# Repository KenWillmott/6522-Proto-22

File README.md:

# 6522-Proto-22
6522 VIA and prototyping board for M8 bus

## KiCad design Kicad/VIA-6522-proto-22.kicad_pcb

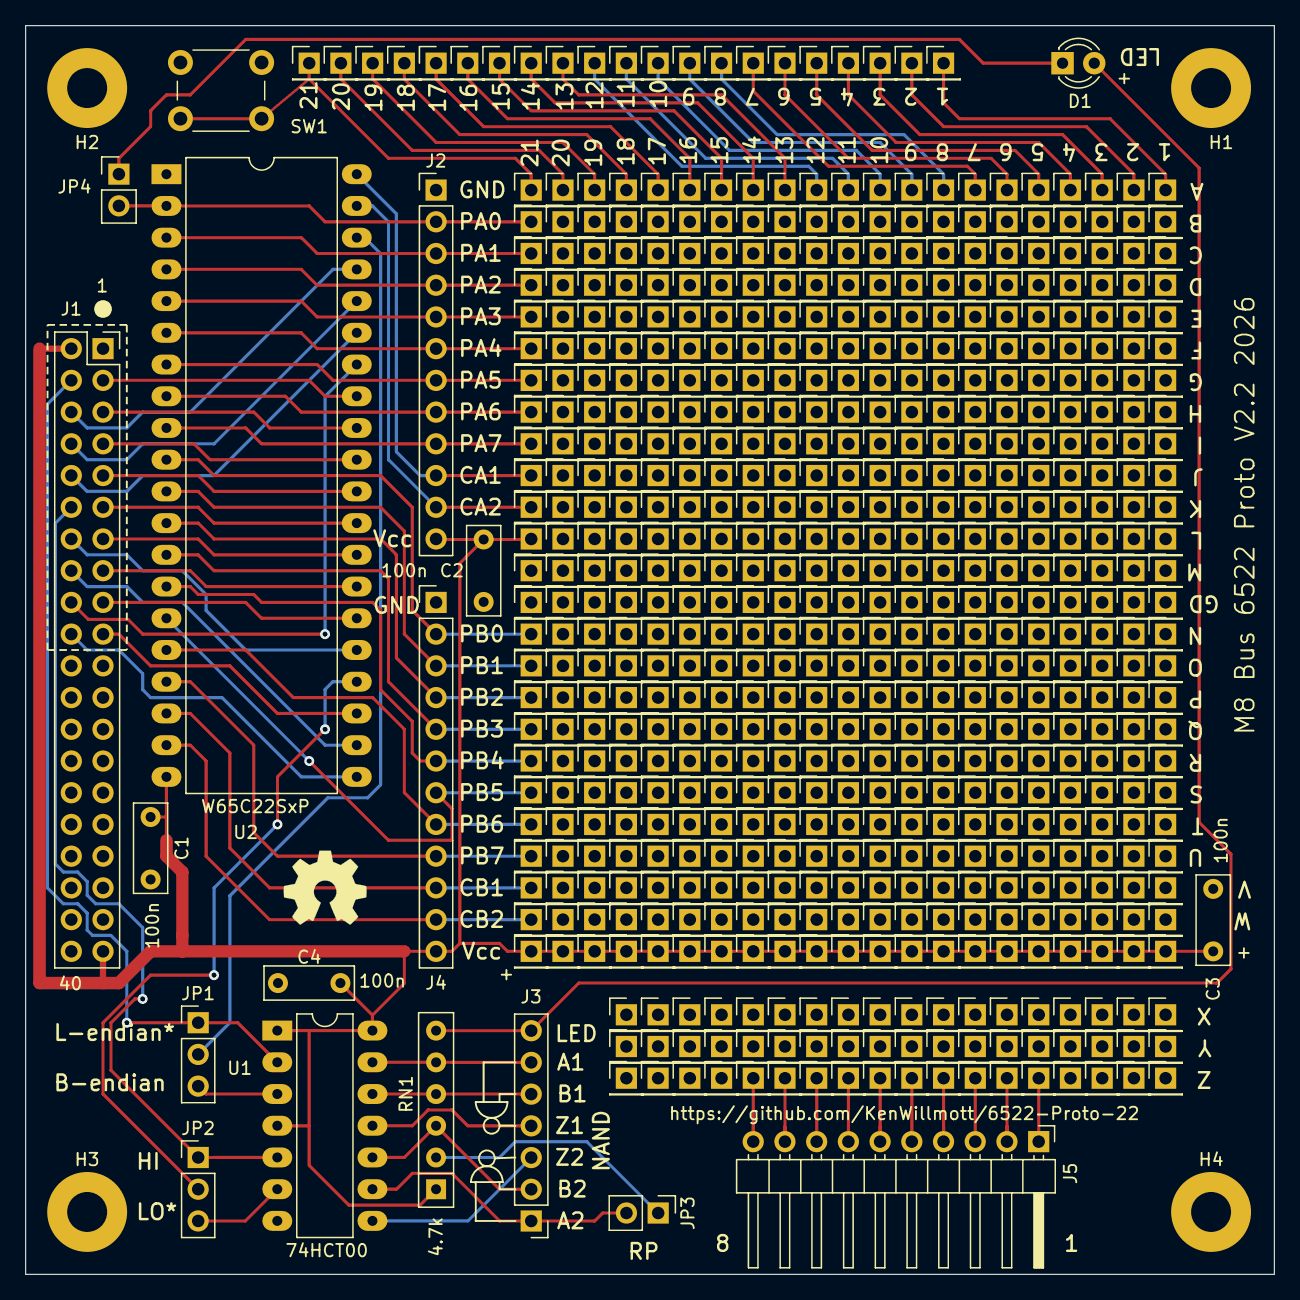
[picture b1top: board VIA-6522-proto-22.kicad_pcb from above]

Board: 2 copper layers, 100.0 x 100.0 mm, 22 parts (0 on the bottom side), 53 nets.

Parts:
C1, C2, C3, C4: 100n; C_Disc_D7.0mm_W2.5mm_P5.00mm
D1: LED; LED_D3.0mm
H1, H2, H3, H4: MountingHole_Pad; MountingHole_3.2mm_M3_Pad
J1: Conn_02x20_Odd_Even; PinSocket_2x20_P2.54mm_Vertical
J2, J4: Conn_01x12_Pin; PinHeader_1x12_P2.54mm_Vertical
J3: Conn_01x07_Pin; PinHeader_1x07_P2.54mm_Vertical
J5: PinHeader_1x10_P2.54mm_Horizontal
JP1, JP2: Jumper_3_Open; PinHeader_1x03_P2.54mm_Vertical
JP3: Jumper_2_Bridged; PinHeader_1x02_P2.54mm_Vertical
JP4: Jumper_2_Open; PinHeader_1x02_P2.54mm_Vertical
RN1: 4.7k; R_Array_SIP6
SW1: SW_Omron_B3FS; SW_PUSH_6mm_H4.3mm
U1: 74HCT00; DIP-14_W7.62mm_LongPads
U2: W65C22SxP; DIP-40_W15.24mm_LongPads

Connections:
/A0: J1.4, JP1.1 (A), U1.2
/A0S: JP1.2 (C), U2.38 (RS0)
/A1: J1.6, U2.37 (RS1)
/A2: J1.8, U2.36 (RS2)
/A3: J1.10, U2.35 (RS3)
/A4: J1.12, JP2.1 (A), U1.5
/A4S: JP2.2 (C), U2.24 (CS1)
/D0: J1.3, U2.33 (D0)
/D1: J1.5, U2.32 (D1)
/D2: J1.7, U2.31 (D2)
/D3: J1.9, U2.30 (D3)
/D4: J1.11, U2.29 (D4)
/D5: J1.13, U2.28 (D5)
/D6: J1.15, U2.27 (D6)
/D7: J1.17, U2.26 (D7)
/bus/BSEL0*: J1.19, U2.23 (~CS2)
/bus/E: J1.14, U2.25 (ϕ2)
/bus/IRQ: J1.20, U2.21 (~IRQ)
/bus/RES: J1.18, U2.34 (~RES)
/bus/RW: J1.16, U2.22 (R/~W)
GND: C1.2, C2.2, C3.2, C4.2, H1.1 (1_1), H2.1 (1_1), H3.1 (1_1), H4.1 (1_1), J1.1, J1.40, J2.1, J4.1, SW1.1, U1.7 (GND), U2.1 (VSS)
unnamed: D1.2 (A), J3.7, RN1.6 (R5)
unnamed: D1.1 (K), JP4.1 (A)
unnamed: J2.3, U2.3 (PA1)
unnamed: J2.4, U2.4 (PA2)
unnamed: J2.5, U2.5 (PA3)
unnamed: J2.6, U2.6 (PA4)
unnamed: J2.7, U2.7 (PA5)
unnamed: J2.8, U2.8 (PA6)
unnamed: J2.9, U2.9 (PA7)
unnamed: J2.10, U2.40 (CA1)
unnamed: J2.11, U2.39 (CA2)
unnamed: J3.1, JP3.2 (B), U1.9
unnamed: J3.2, RN1.3 (R2), U1.10
unnamed: J3.3, U1.8
unnamed: J3.4, U1.11
unnamed: J3.5, RN1.4 (R3), U1.12
unnamed: J3.6, RN1.5 (R4), U1.13
unnamed: J4.2, U2.10 (PB0)
unnamed: J4.3, U2.11 (PB1)
unnamed: J4.4, U2.12 (PB2)
unnamed: J4.5, U2.13 (PB3)
unnamed: J4.6, U2.14 (PB4)
unnamed: J4.7, U2.15 (PB5)
unnamed: J4.8, U2.16 (PB6)
unnamed: J4.9, U2.17 (PB7)
unnamed: J4.10, U2.18 (CB1)
unnamed: J4.11, U2.19 (CB2)
unnamed: JP1.3 (B), U1.3
unnamed: JP2.3 (B), U1.6
unnamed: JP3.1 (A), RN1.2 (R1)
PA0: J2.2, JP4.2 (B), U2.2 (PA0)
VCC: C1.1, C2.1, C3.1, C4.1, J1.2, J1.39, J2.12, J4.12, RN1.1 (common), U1.1, U1.4, U1.14 (VCC), U2.20 (VCC)
